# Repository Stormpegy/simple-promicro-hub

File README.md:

# simple-promicro-hub
Simple 58mm round promicro breakout board for DIY sim racing wheel  
Kicad 5.1.4 as always, Uses Sparkfun Kicad libraries  
Made for a DIY aliexpress simracing wheel with 3d printed components  

This work is licensed by [stormpegy](https://github.com/Stormpegy/) under [CC BY-SA 4.0](https://creativecommons.org/licenses/by-sa/4.0/)

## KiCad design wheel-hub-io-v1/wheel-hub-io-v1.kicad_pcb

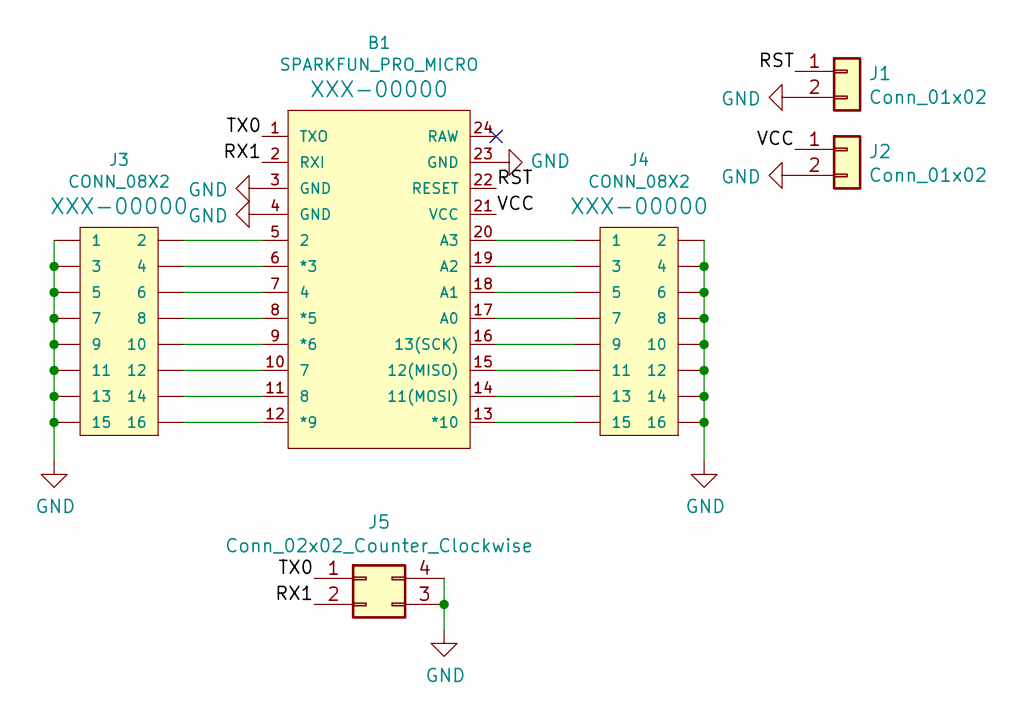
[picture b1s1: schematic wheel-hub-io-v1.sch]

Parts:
B1: SPARKFUN_PRO_MICRO
J1, J2: Conn_01x02; Pin_Header_Straight_1x02_Pitch2.54mm
J3, J4: CONN_08X2; Pin_Header_Straight_2x08_Pitch2.54mm
J5: Conn_02x02_Counter_Clockwise; Pin_Header_Straight_2x02_Pitch2.54mm

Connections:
/RST: B1.22 (RESET), J1.1
/RX1: B1.2 (RXI), J5.2
/TX0: B1.1 (TXO), J5.1
/VCC: B1.21 (VCC), J2.1
GND: B1.3 (GND), B1.4 (GND), B1.23 (GND), J1.2, J2.2, J3.1, J3.3, J3.5, J3.7, J3.9, J3.11, J3.13, J3.15, J4.2, J4.4, J4.6, J4.8, J4.10, J4.12, J4.14, J4.16, J5.3, J5.4
unnamed: B1.5 (2), J3.2
unnamed: B1.6 (*3), J3.4
unnamed: B1.7 (4), J3.6
unnamed: B1.8 (*5), J3.8
unnamed: B1.9 (*6), J3.10
unnamed: B1.10 (7), J3.12
unnamed: B1.11 (8), J3.14
unnamed: B1.12 (*9), J3.16
unnamed: B1.13 (*10), J4.15
unnamed: B1.14 (11(MOSI)), J4.13
unnamed: B1.15 (12(MISO)), J4.11
unnamed: B1.16 (13(SCK)), J4.9
unnamed: B1.17 (A0), J4.7
unnamed: B1.18 (A1), J4.5
unnamed: B1.19 (A2), J4.3
unnamed: B1.20 (A3), J4.1

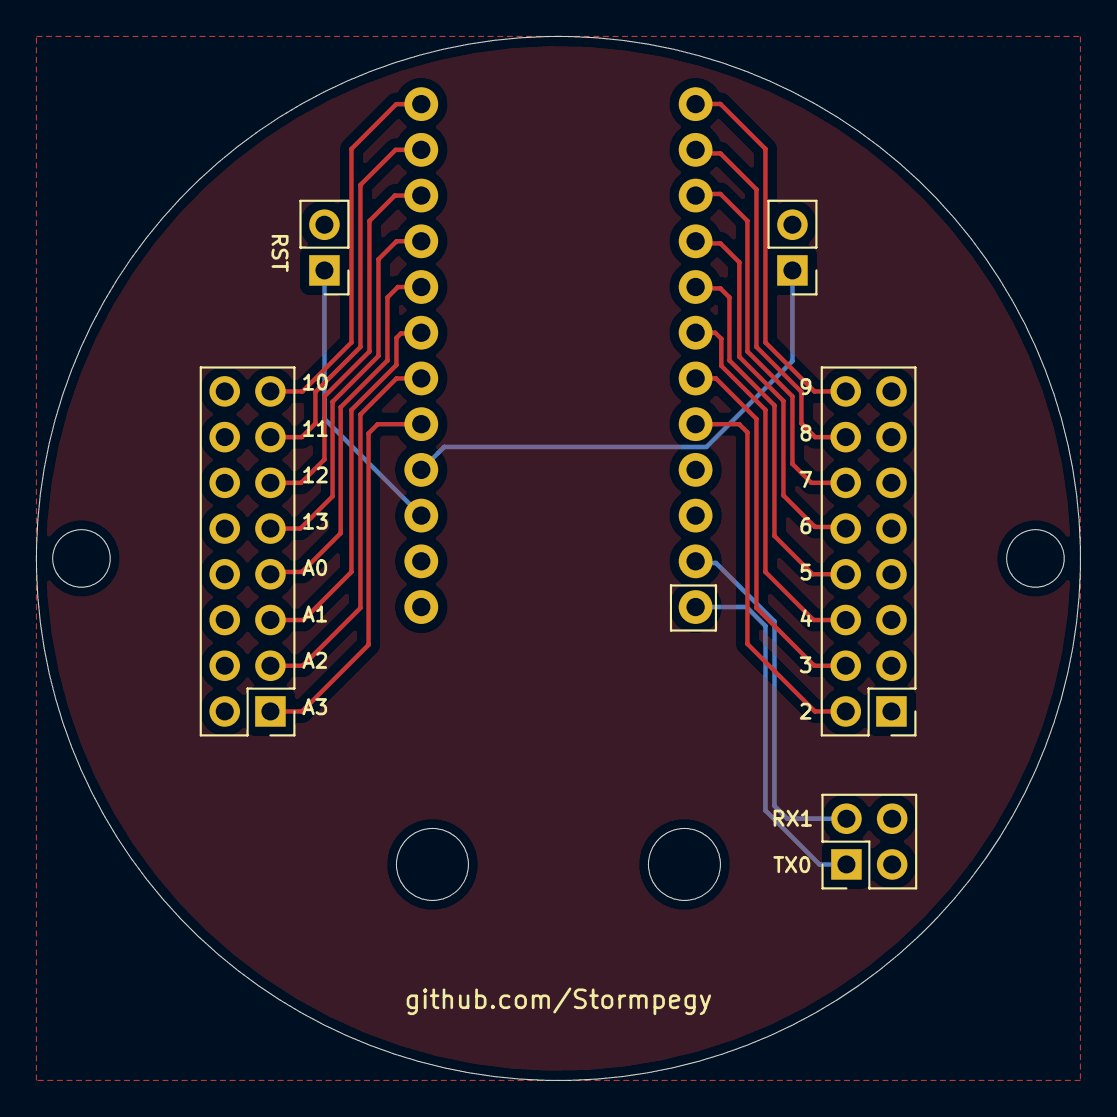
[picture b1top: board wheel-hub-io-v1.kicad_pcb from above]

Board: 2 copper layers, 58.0 x 58.0 mm, 6 parts (0 on the bottom side), 21 nets.

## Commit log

2021-04-22 readme!
    image!
2021-04-22 ok i'm dumb
2021-04-24 license :sunglasses:
